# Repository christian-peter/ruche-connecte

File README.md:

# !!! EN COURS DE REDACTION !!! 
donc incomplet et en évolution à un rythme aléatoire

# Outil de suivi de ruchers
Ce projet est en cours de développement. Tous les éléments décrits dans le synoptique ne sont donc pas fonctionnels à ce jour.

Certains éléments ont été développés par des apprentis ingénieurs suivant la formation "électronique et informatique industrielle" à 
[Polytech Nice Sophia](http://unice.fr/polytechnice/fr). Une page spécifique à ce projet est disponible [ici](http://rucher.polytech.unice.fr/).  

L'objectif consiste à relever différents paramètres (masse, vibrations, température et hygrométrie interne à la ruche, données météorologiques) pour les rendre accessibles à distance via des périphériques tels qu'un ordinateur, une tablette, un smartphone ....  
 
Afin de remplir ces différentes fonctions, le système global à été scindé en plusieurs blocs. Les fonctions des trois premiers modules, qui doivent être autonomes en énergie, sont les suivantes :

* relever la masse de la ruche ;
* mesurer les grandeurs internes (températures, hygrométrie, vibrations, ....) ;
* mesurer les données météorologiques (température, hygrométrie, vent, pluie, ensoleillement, ...).

Les données relevées par ces modules sont transmises via un réseau LoRa, dont la portée doit être importante, à une passerelle dont la fonction consiste à enregistrer ces mesures dans une base de données. Ces données sont alors rendues accessibles via un serveur "web". 

L'électronique a été développée autour d'un microcontrôleur [ESP32](http://esp32.net/) d'Espressif Systems, basé sur l'architecture Xtensa LX6 de Tensilica, intégrant la gestion du Wi-Fi et du Bluetooth et d'un modem LoRa [RFM95](https://www.hoperf.com/modules/lora/RFM95.html).

Elle a été conçue avec un soucis de polyvalence pour permettre différentes configurations mais aussi pour faciliter les évolutions ou optimisations futures. C'est la cas notamment pour l'alimentation des différents modules.

## L'alimentation des modules

La tension d'alimentation des circuits précités est de 3.3V (maxi 3.6V). Il peuvent donc être alimentés directement par des batteries lithium-fer-phosphate (LiFePO<sub>4</sub>). Afin de pouvoir utiliser également d'autres sources d'énergie (batteries Lipo, Liion, plomb, .... ) les cartes sont équipées d'un régulateur de tension (MIC5239).

Une carte batterie spécifique peut être connectée via les connecteurs JP2 et JP3, elle peut être équipée d'une batterie LiFePO<sub>4</sub> connectée entre la masse et le signal '3.3_BAT'.

En l'absence d'alimentation sur l'entrée '+12V', le transistor Q4 est passant alimentant ainsi les éléments connectés à 'Vcc' à partir de la batterie LiFePO<sub>4</sub>. 

Si la carte est alimentée par l'entrée '+12V', les éléments connectés à 'Vcc' sont alimentés par le régulateur MIC5239. Le transistor Q4 est bloqué car le régulateur ne doit pas charger la batterie. L'entrée '+12V' peut recevoir des tensions comprises entre 3.6V et 30V. 
<!-- Les cartes sont généralement prévues pour recevoir un régulateur en boîtier :

* soit SOT-223,
* soit MSOP.-->

Dans le but d'économiser l'énergie, les périphériques ne sont alimentés par 'V+' que lorsque le transistor Q1 est passant (cad lorsque la sortie 'MEASURE' de l'ESP32 est au niveau haut).

## La programmation du microcontrôleur

Le logiciel est développé sur l'interface arduino. L’installation et l'utilisation de cet outil est décrit
[ici](https://www.arduino-france.com/tutoriels/ide-arduino-installation-et-utilisation/).

Il faut le configurer pour pouvoir utiliser l'ESP32 : voir 
[ce site](http://electroniqueamateur.blogspot.com/2019/07/programmer-lesp32-avec-lide-arduino.html)
ou [celui-ci](http://emery.claude.free.fr/esp32-idearduino.html).

Sauf erreur et/ou oubli, les librairies utilisées sont : 

* [DebugUtils](https://github.com/SensorsIot/DebugUtils/blob/master/DebugUtils/DebugUtils.h)
* [LoRa (Sandeep Mistry)](https://github.com/sandeepmistry/arduino-LoRa)
* [esp8266-oled-ssd1306](https://github.com/ThingPulse/esp8266-oled-ssd1306)
* [SparkFun NAU7802](https://github.com/sparkfun/SparkFun_Qwiic_Scale_NAU7802_Arduino_Library)
* [OneWire](https://www.pjrc.com/teensy/td_libs_OneWire.html)
* [CRC32](https://github.com/bakercp/CRC32)
* [MAX17263-fuel-gauge](https://github.com/avandalen/Arduino-MAX17263-fuel-gauge-library)
* [Streaming](https://github.com/janelia-arduino/Streaming)

Le téléversement nécessite un interface 
[USB/FTDI232](https://www.google.com/search?q=ftdi232&tbm=isch&ved=2ahUKEwj_ld-KopTvAhUEgM4BHXQxAnQQ2-cCegQIABAA&oq=ftdi232&gs_lcp=CgNpbWcQAzIECCMQJzIECCMQJzICCAAyAggAMgQIABAeMgQIABAeMgQIABAeMgQIABAeMgQIABAeMgYIABAKEBhQ8tsCWPLbAmDG3QJoAHAAeACAAViIAViSAQExmAEAoAEBqgELZ3dzLXdpei1pbWfAAQE&sclient=img&ei=FZQ_YL-3KYSAur4P9OKIoAc&bih=596&biw=1417&client=ubuntu&hs=15p).

Les connexions minimales à établir sont :

* ESP32 gnd <=> FTDI232 gnd (noir)
* ESP32 Tx <=> FTDI232 Rx (orange)
* ESP32 Rx <=> FTDI232 Tx (jaune)

Si le module n'est pas alimenté de façon autonome, il faut ajouter un fil d'alimentation (Vcc) et le cavalier jaune (voir la flèche) doit être positionné coté 3.3V, si le module dispose de sa propre alimentation il faut retirer le cavalier.

* ESP32 Vcc <=> FTDI232 Vcc (rouge)

Pour activer le mode téléversement il faut : appuyer sur le bouton 'PROG', appuyer et relâcher le bouton 'RST', 
relâcher le bouton 'PROG'.

Pour automatiser le transfert, j'ai développé un 
[petit module](/usb-ftdi232/README.md)
sur lequel on peut souder le module FTDI 232. 
Les connexions sont alors à réaliser sur le circuit secondaire et il faut ajouter :

* ESP32 IO0 <=> FTDI232 IO0 (vert)
* ESP32 RST <=> FTDI232 RST (marron)

Le connecteur JST permet d'alimenter l'ESP32, il faut alors retirer le cavalier d'alimentation.

# La réalisation 

* [la balance](/Balance/README.md#la-balance)
* le module interne
* le module météorologique
* la carte batterie
* la passerelle (gateway)

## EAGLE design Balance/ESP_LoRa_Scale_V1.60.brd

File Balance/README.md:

# LA BALANCE

## Préambule

Pour la partie mécanique qui ne sera pas développée ici (mis à part quelques photos de prototypes), je me suis inspiré des balances trouvées dans le commerce dont les capteurs de force sont de ce type :

Mon premier prototype avec un capteur n'était pas assez stable à mon gout. J'en ai donc réalisé 
[d'autres](/Balance/Images/proto_meca.png) avec 2 capteurs puis 4 capteurs. 

J'ai aussi testé les capteurs utilisés pour les pèse-personnes.

L'électronique est donc conçue pour s'adapter à ces différentes configurations. 

## Fonctionnement

Après mise sous tension, le module entre en mode sommeil pour réduire la consommation au maximum.
Il se réveille à intervalles réguliers. Il mesure alors la masse et envoie les données (avec un code d'erreur CRC) via un réseau LoRa puis attend un accusé de réception. A réception d'un accusé de réception valide, le module repasse en mode sommeil ; si l'accusé de réception n'est pas valide, les données sont renvoyées (au maximum 'send_max_tries' fois). Sans accusé de réception au bout de 'WAIT_TIME_FOR_ACKNOWLEDGE' le module passe en mode sommeil.

La durée de sommeil est paramétrable et différenciée entre jour et nuit. La période 'jour' débute 1 heure avant le début du jour et s'achève 1 heure après la fin du jour.

Le module peut aussi être réveillé manuellement par un appui bref sur la touche capacitive gauche ; un menu à dérouler avec la touche capacitive droite permet alors de sélectionner différentes actions ou d'afficher différentes informations :

* création d'une visite (dans la base de données),
* mise en sommeil,
* nourrissement 50/50 (1),
* nourrissement 70/30 (1),
* nourrissement candy (1),
* modification matérielle (1),
* mesure de la masse,
* informations batterie,
* informations version et numéro de balance,
* informations LoRa,
* informations température capteurs.

Une fois le choix validé par la touche capacitive gauche, les données sont envoyées ou les informations affichées et le module retourne au mode sommeil.

(1) L'information ainsi que la variation de masse correspondante est stockée dans la base de données.

## Calibration et réglages

Un appui maintenu sur la touche capacitive gauche permet d'accéder à la procédure de calibration ou au réglage des paramètres.

### Calibration

Avant la première utilisation, il faut calibrer la balanceen suivant les indications affichées sur l'écran LCD.

### Réglages

Un certain nombre de paramètres sont modifiables en se connectant au module en Bluetooth avec un terminal série : par exemple 
[Serial Bluetooth Terminal](https://play.google.com/store/apps/details?id=de.kai_morich.serial_bluetooth_terminal&hl=fr&gl=US).

Les paramètres sont regroupés par famille et sont les suivants :

* réglages généraux :
    - intervalle de mesure le jour,
    - intervalle de mesure la nuit,
    - intervalle de mesure pour visite,
    - nombre maximum de transmission,
    - numéro de la balance,
    - variation de masse générant une alerte,
* réglages LoRa :
    - fréquence, 
    - facteur d’étalement de spectre (7 à 12; 12 <=> portée maximale, mais autonomie plus faible),
    - bande passante,
    - puissance d'émission (7 à 15 dB <=> portée maximale, mais autonomie plus faible),
* dérive des capteurs en température,
* initialisation de la mémoire EEPROM (reset des paramètres de calibration et autres réglages).

exemple vidéo : [mp4](http://rucher.polytech.unice.fr/ruche-connecte/videos/reglages.mp4) 
[wmv](http://rucher.polytech.unice.fr/ruche-connecte/videos/reglages.wmv)
<!-- 
ffmpeg -i /tmp/reglages.mp4 -vf scale=960:-1  -an output2.mp4
https://www.linuxtricks.fr/wiki/ffmpeg-la-boite-a-outils-multimedia
https://tuxicoman.jesuislibre.net/2017/01/changer-la-resolution-dune-video-avec-ffmpeg-sous-linux.html
-->

## Electronique

Les schémas et PCB sont dessinés avec [eagle](https://www.autodesk.com/products/eagle/overview?plc=F360&term=1-YEAR&support=ADVANCED&quantity=1) :

* [schéma](/Balance/ESP_LoRa_Scale_V1.60.sch)
* [pcb](/Balance/ESP_LoRa_Scale_V1.60.brd)
* [gerber](/Balance/gerber/ESP_LoRa_Scale_V1.60.zip)
* [liste du matériel](/Balance/ESP_LoRa_Scale_V1.60.csv)

L'[antenne 'UCA'](http://users.polytech.unice.fr/~ferrero/recherche_UCAboards.html) 
LoRa, déssinée par Fabien Ferrero, est supportée par le circuit imprimé. 
Pour une efficacité maximale de l'antenne, ce dernier doit être réalisé en FR4 avec une épaisseur de 0,8mm.

Il est aussi possible de connecter une antenne externe via un connecteur UFL, la piste reliée à l'antenne 'UCA'
doit alors être coupée.  

Cette carte peut recevoir 1, 2 ou 4 capteurs de force. Le convertisseur NAU7802 U4 et les composants associés
ne sont utiles que pour l'utilisation de 4 capteurs ; le pont SJ7 doit alors être court-circuité.
Avec 1 ou 2 capteurs on laisse SJ7 ouvert pour réduire la consommation et on utilise les entrées du convertisseur U2.
Un capteur unique doit être connecté sur les entrées 'A', les entrées 'B' étant reliées à la masse.

Le connecteur 'JP3' permet de connecter un capteur de température dans le but de compenser les dérives thermiques des capteurs de force. Pour l'instant seul est supporté le capteur de type 18B20. On pourrait aussi utiliser des capteurs de la famille DHT11,
permettant d'obtenir aussi une mesure d'hygrométrie mais la partie software devra être modifiée en conséquence.

## Logiciel

L'archive est à extraire dans le dossier 'projet' de l'IDE arduino.

* [ESP_LoRa_Scale_V0.34.zip](/Balance/ESP_LoRa_ScaleV0.34.zip)

Hormis la mesure de tension de la batterie, la partie 'fuel gauge' reste à développer.

## Mesures

à venir

## Prototypes

aussi

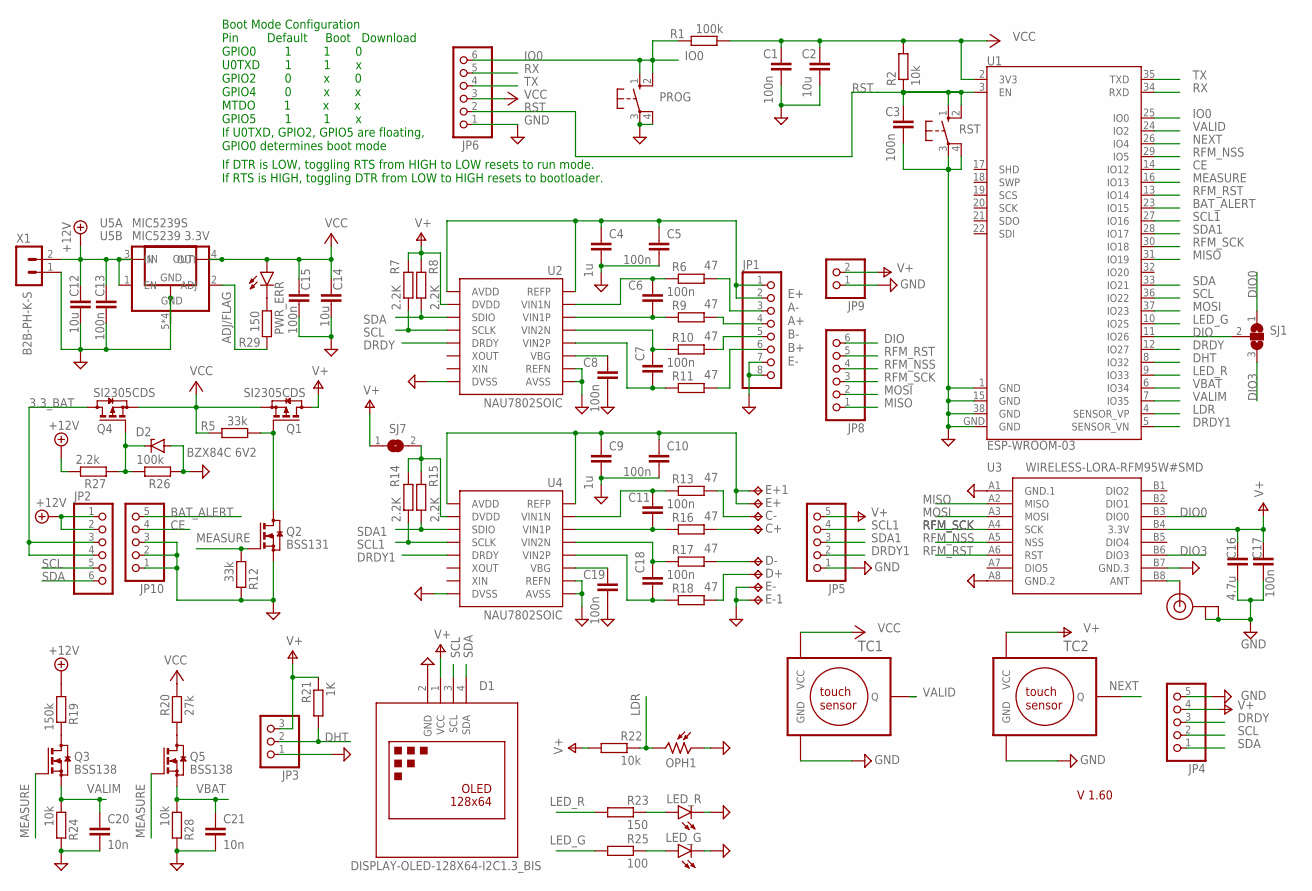
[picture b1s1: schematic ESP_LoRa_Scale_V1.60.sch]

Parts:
C1, C3, C5, C6, C7, C8, C10, C11, C13, C15, C17, C18, C19: 100n; C1206
C2, C12, C14: 10u; C1210
C4, C9: 1u; C1210
C16: 4.7u; C1210
C20, C21: 10n; C1206
C+: TPTP17SQ; TP17SQ
C-: TPTP17SQ; TP17SQ
D1: DISPLAY-OLED-128X64-I2C1.3_BIS; DISPLAY-OLED-128X64-1.3-I2C_BIS
D2: BZX84C 6V2; TO236
D+: TPTP17SQ; TP17SQ
D-: TPTP17SQ; TP17SQ
E+, E+1: TPTP17SQ; TP17SQ
E-, E-1: TPTP17SQ; TP17SQ
J1: U.FL
JP1: PINHD-1X8; 1X08
JP2, JP6, JP8: PINHD-1X6; 1X06
JP3: PINHD-1X3; 1X03
JP4, JP5, JP10: PINHD-1X5; 1X05
JP9: PINHD-1X2; 1X02
LED_G: LEDSMT1206; 1206
LED_R: LEDSMT1206; 1206
OPH1: VT93N2; VT900
PROG: 10-XX; B3F-10XX
PWR_ERR: LEDSMT1206; 1206
Q1, Q4: SI2305CDS; SOT23
Q2: BSS131; SOT23
Q3, Q5: BSS138; SOT23
R1, R26: 100k; R1206
R2, R22, R24, R28: 10k; R1206
R5, R12: 33k; R1206
R6, R9, R10, R11, R13, R16, R17, R18: 47; R1206
R7, R8, R14, R15: 2.2K; R1206
R19: 150k; R1206
R20: 27k; R1206
R21: 1K; R1206
R23, R29: 150; R1206
R25: 100; R1206
R27: 2.2k; R1206
RST: 10-XX; B3F-10XX
SJ1: SJ2W; SJ_2
SJ7: SJ
TC1, TC2: TTP223R_H; TTP233RED_H
U1: ESP-WROOM-03
U2, U4: NAU7802SOIC; SO16
U3: WIRELESS-LORA-RFM95W#SMD
U5A: MIC5239 3.3V; MSOP08
U5B: MIC5239S; SOT223
X1: B2B-PH-K-S

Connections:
3.3_BAT: JP2.3, JP2.4, Q4.3 (D)
+12V: C12.1, C13.1, JP2.1, JP2.2, R19.1, R27.2, U5A.1 (EN), U5A.3 (IN), U5B.1 (IN), X1.2
A+: JP1.4, R9.2
A-: JP1.3, R6.2
ADJ/FLAG: R29.2, U5A.2 (ADJ)
ANT: J1.3 (SIGNAL), U3.B8 (ANT)
B+: JP1.6, R11.2
B-: JP1.5, R10.2
BAT_ALERT: JP10.5, U1.23 (IO15)
CE: JP10.4, U1.14 (IO12)
DHT: JP3.2, R21.1, U1.8 (IO32)
DIO: JP8.6, SJ1.2, U1.11 (IO26)
DIO0: SJ1.1, U3.B3 (DIO0)
DIO3: SJ1.3, U3.B6 (DIO3)
DRDY: JP4.3, U1.12 (IO27), U2.12 (DRDY)
DRDY1: JP5.2, U1.5 (SENSOR_VN), U4.12 (DRDY)
GND: C1.2, C2.2, C3.2, C4.2, C5.2, C8.2, C9.2, C10.2, C12.2, C13.2, C14.2, C15.2, C16.2, C17.2, C19.2, C20.2, C21.2, D1.2 (GND), D2.A, E-.TP, E-1.TP, J1.1 (GND), J1.2 (GND), JP1.7, JP1.8, JP3.1, JP4.5, JP5.1, JP6.1, JP9.1, JP10.1, JP10.2, JP10.3, LED_G.C, LED_R.C, OPH1.1, PROG.3, PROG.4 (P1), Q2.2 (S), R12.2, R24.2, R26.1, R28.2, RST.3, RST.4 (P1), TC1.P$3 (GND), TC2.P$3 (GND), U1.1 (GND), U1.15 (GND), U1.38 (GND), U1.GND, U2.7 (REFN), U2.8 (AVSS), U2.9 (DVSS), U3.A1 (GND.1), U3.A8 (GND.2), U3.B7 (GND.3), U4.7 (REFN), U4.8 (AVSS), U4.9 (DVSS), U5A.5 (GND), U5A.6 (GND), U5A.7 (GND), U5A.8 (GND), U5B.2 (GND), U5B.4 (GND), X1.1
IO0: JP6.6, PROG.1 (S), PROG.2 (S1), R1.2, U1.25 (IO0)
LDR: OPH1.2, R22.2, U1.4 (SENSOR_VP)
LED_G: R25.1, U1.10 (IO25)
LED_R: R23.1, U1.9 (IO33)
MEASURE: Q2.1 (G), Q3.1 (G), Q5.1 (G), R12.1, U1.16 (IO13)
MISO: JP8.1, U1.31 (IO19), U3.A2 (MISO)
MOSI: JP8.2, U1.37 (IO23), U3.A3 (MOSI)
unnamed: Q1.1 (G), Q2.3 (D), R5.1
unnamed: Q3.3 (D), R19.2
unnamed: R14.2, R15.2, SJ7.2, U4.15 (DVDD)
unnamed: Q5.3 (D), R20.1
unnamed: PWR_ERR.C, R29.1
unnamed: LED_R.A, R23.2
unnamed: LED_G.A, R25.2
unnamed: C8.1, U2.6 (VBG)
unnamed: C19.1, U4.6 (VBG)
unnamed: C11.2, R16.1, U4.3 (VIN1P)
unnamed: C11.1, R13.1, U4.2 (VIN1N)
unnamed: C6.2, R9.1, U2.3 (VIN1P)
unnamed: C6.1, R6.1, U2.2 (VIN1N)
unnamed: C7.1, R10.1, U2.4 (VIN2N)
unnamed: C7.2, R11.1, U2.5 (VIN2P)
unnamed: C18.1, R17.1, U4.4 (VIN2N)
unnamed: C18.2, R18.1, U4.5 (VIN2P)
unnamed: D+.TP, R18.2
unnamed: D-.TP, R17.2
unnamed: C9.1, C10.1, E+.TP, E+1.TP, U4.1 (REFP), U4.16 (AVDD)
unnamed: C-.TP, R13.2
unnamed: C+.TP, R16.2
unnamed: C4.1, C5.1, JP1.1, JP1.2, U2.1 (REFP), U2.16 (AVDD)
unnamed: D2.C, Q4.1 (G), R26.2, R27.1
NEXT: TC2.P$2 (Q), U1.26 (IO4)
RFM_NSS: JP8.4, U1.29 (IO5), U3.A5 (NSS)
RFM_RST: JP8.5, U1.13 (IO14), U3.A6 (RST)
RFM_SCK: JP8.3, U1.30 (IO18), U3.A4 (SCK)
RST: C3.1, JP6.2, R2.1, RST.1 (S), RST.2 (S1), U1.3 (EN)
RX: JP6.5, U1.34 (RXD)
SCL: D1.3 (SCL), JP2.5, JP4.2, R7.1, U1.36 (IO22), U2.13 (SCLK)
SCL1: JP5.4, R14.1, U1.27 (IO16), U4.13 (SCLK)
SDA: D1.4 (SDA), JP2.6, JP4.1, R8.1, U1.33 (IO21), U2.14 (SDIO)
SDA1: JP5.3, R15.1, U1.28 (IO17), U4.14 (SDIO)
TX: JP6.4, U1.35 (TXD)
V+: C16.1, C17.1, D1.1 (VCC), JP3.3, JP4.4, JP5.5, JP9.2, Q1.3 (D), R7.2, R8.2, R21.2, R22.1, SJ7.1, TC2.P$1 (VCC), U2.15 (DVDD), U3.B4 (3.3V)
VALID: TC1.P$2 (Q), U1.24 (IO2)
VALIM: C20.1, Q3.2 (S), R24.1, U1.7 (IO35)
VBAT: C21.1, Q5.2 (S), R28.1, U1.6 (IO34)
VCC: C1.1, C2.1, C14.1, C15.1, JP6.3, PWR_ERR.A, Q1.2 (S), Q4.2 (S), R1.1, R2.2, R5.2, R20.2, TC1.P$1 (VCC), U1.2 (3V3), U5A.4 (OUT), U5B.3 (OUT)

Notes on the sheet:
If DTR is LOW, toggling RTS from HIGH to LOW resets to run mode. If RTS is HIGH, toggling DTR from LOW to HIGH resets to bootloader.
Boot Mode Configuration Pin Default Boot Download GPIO0 1 1 0 U0TXD 1 1 x GPIO2 0 x 0 GPIO4 0 x x MTDO 1 x x GPIO5 1 1 x If U0TXD, GPIO2, GPIO5 are floating, GPIO0 determines boot mode
V 1.60
E+ A- A+ B- B+ E-

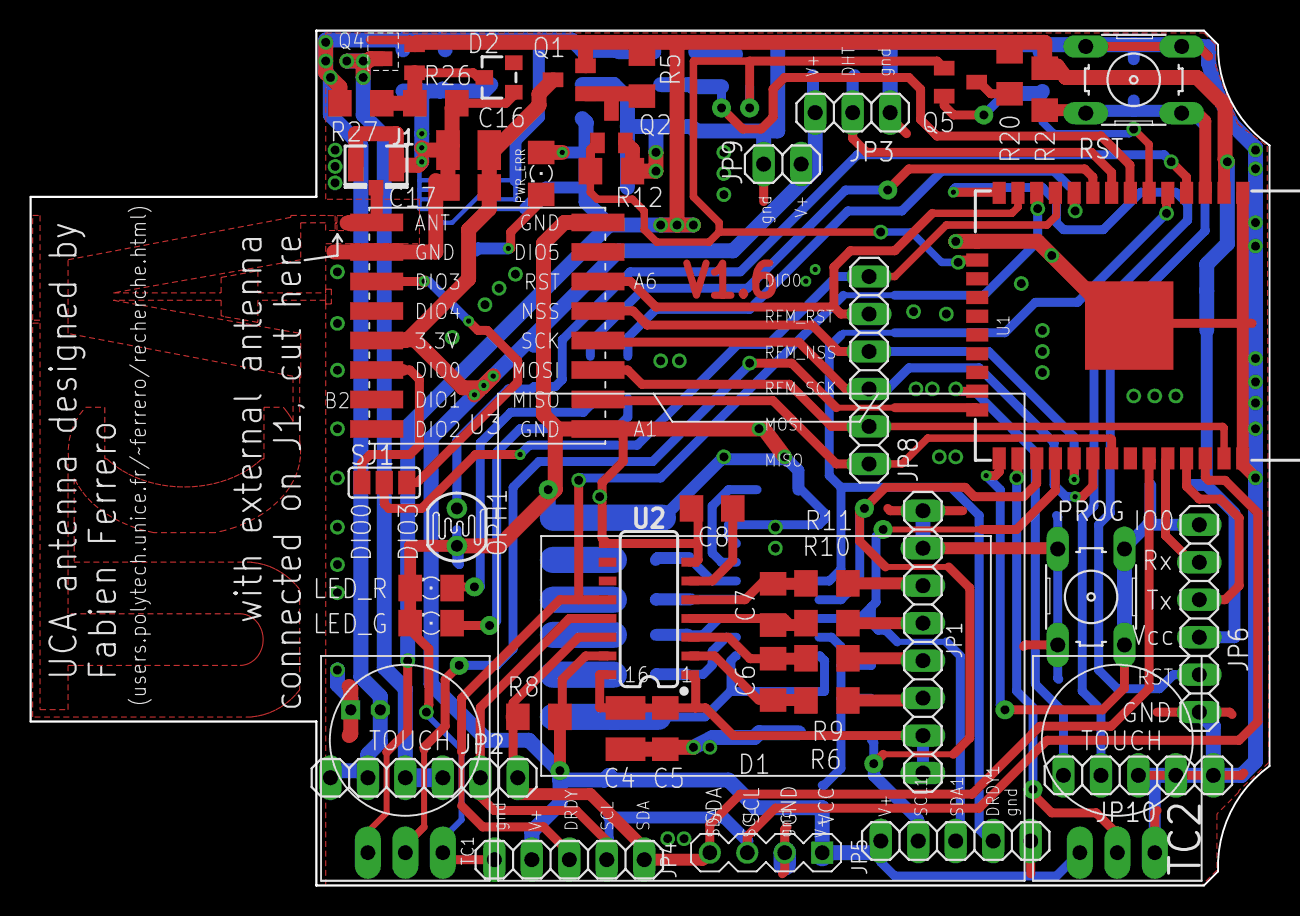
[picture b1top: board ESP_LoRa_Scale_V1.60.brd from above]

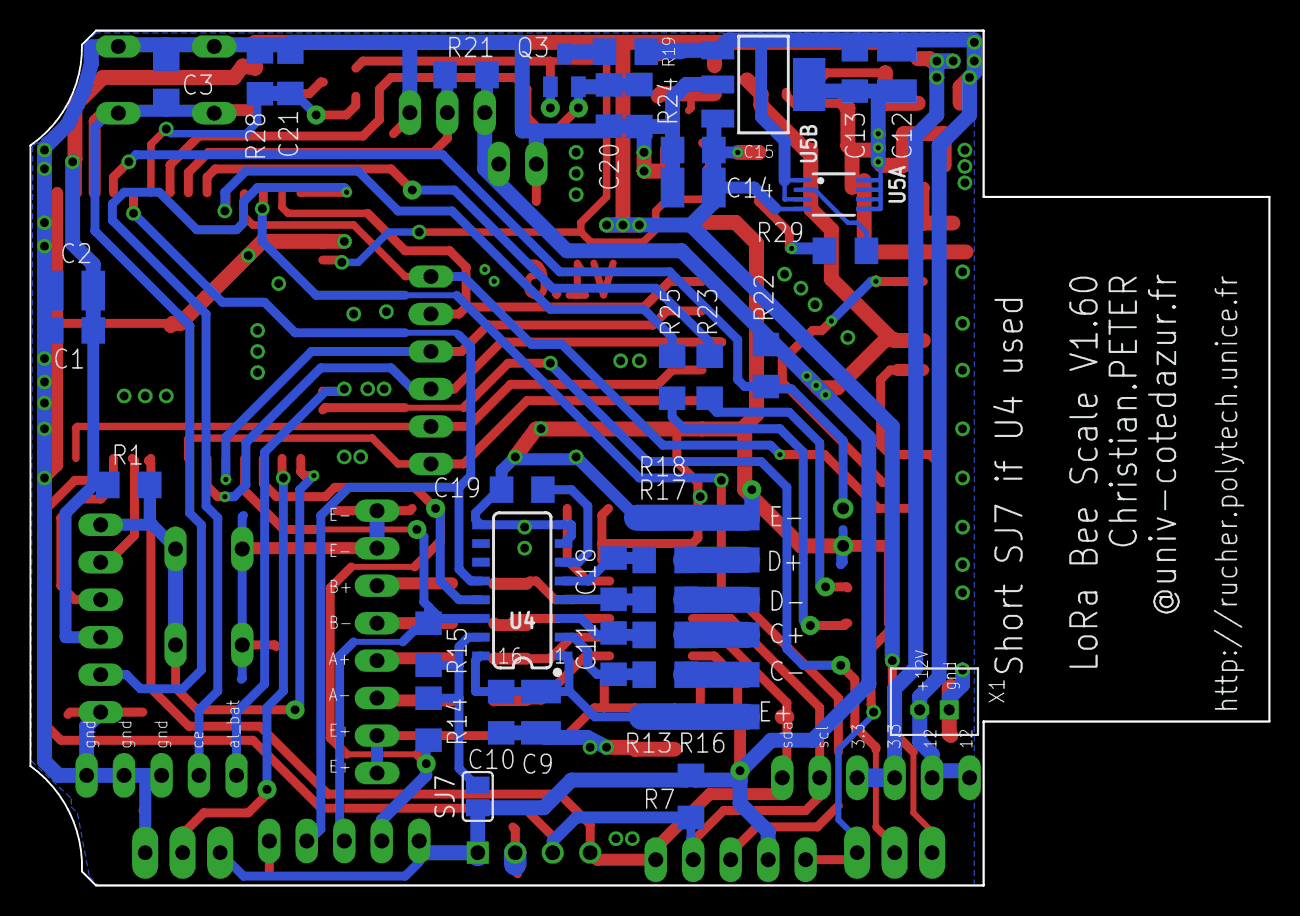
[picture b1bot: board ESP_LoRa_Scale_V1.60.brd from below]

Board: 2 copper layers, 84.0 x 57.9 mm, 90 parts (44 on the bottom side), 64 nets.

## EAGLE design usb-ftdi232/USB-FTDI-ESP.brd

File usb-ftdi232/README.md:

Les schémas et PCB sont dessinés avec [eagle](https://www.autodesk.com/products/eagle/overview?plc=F360&term=1-YEAR&support=ADVANCED&quantity=1) :

* [schéma](/usb-ftdi232/USB-FTDI-ESP.sch)
* [pcb](/usb-ftdi232/USB-FTDI-ESP.brd)
* [gerber](/usb-ftdi232/gerber/USB-FTDI-ESP32.zip)
* [liste du matériel](/usb-ftdi232/USB-FTDI-ESP.csv)

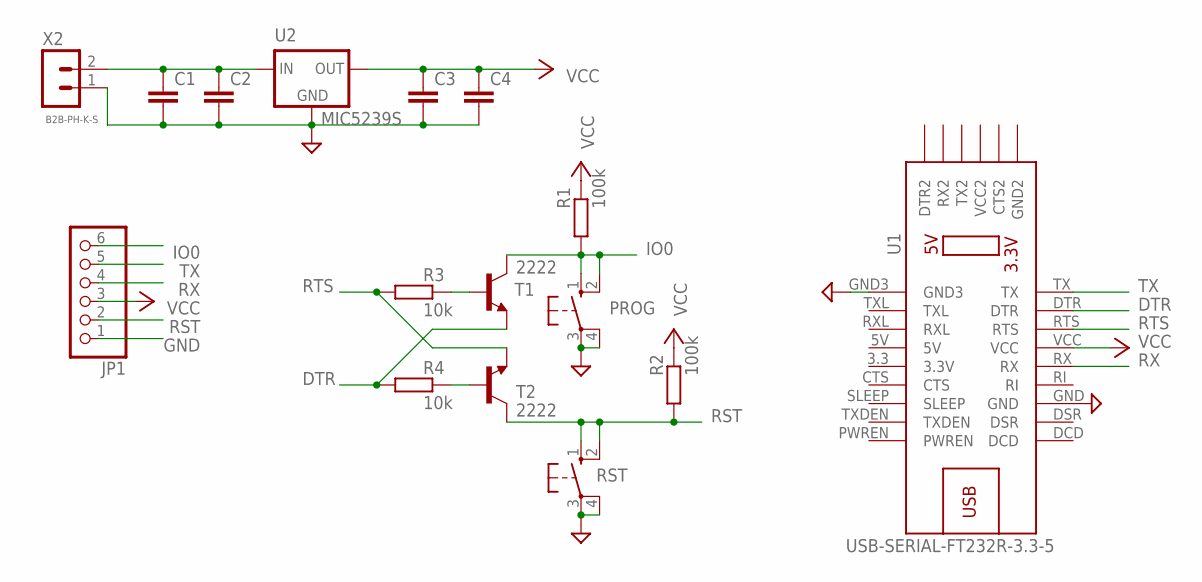
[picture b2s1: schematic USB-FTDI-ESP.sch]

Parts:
C1, C2, C3, C4: C-EUC1206K; C1206K
JP1: PINHD-1X6; 1X06
PROG: 10-XX; B3F-10XX
R1, R2: 100k; R1206
R3, R4: 10k; R1206
RST: 10-XX; B3F-10XX
T1, T2: 2222; SOT23-BEC
U1: USB-SERIAL-FT232R-3.3-5
U2: MIC5239S; SOT223
X2: B2B-PH-K-S

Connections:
DTR: R4.1, T1.E, U1.DTR
GND: C1.2, C2.2, C3.2, C4.2, JP1.1, PROG.3, PROG.4 (P1), RST.3, RST.4 (P1), U1.GND, U1.GND3, U2.2 (GND), U2.4 (GND), X2.1
IO0: JP1.6, PROG.1 (S), PROG.2 (S1), R1.1, T1.C
unnamed: C1.1, C2.1, U2.1 (IN), X2.2
unnamed: R3.2, T1.B
unnamed: R4.2, T2.B
RST: JP1.2, R2.1, RST.1 (S), RST.2 (S1), T2.C
RTS: R3.1, T2.E, U1.RTS
RX: JP1.4, U1.RX
TX: JP1.5, U1.TX
VCC: C3.1, C4.1, JP1.3, R1.2, R2.2, U1.VCC, U2.3 (OUT)
VCC2: U1.VCC2

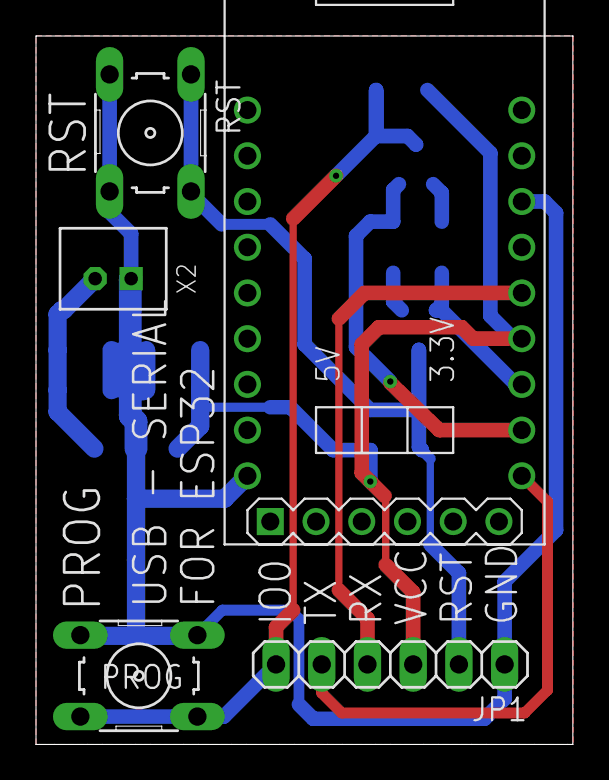
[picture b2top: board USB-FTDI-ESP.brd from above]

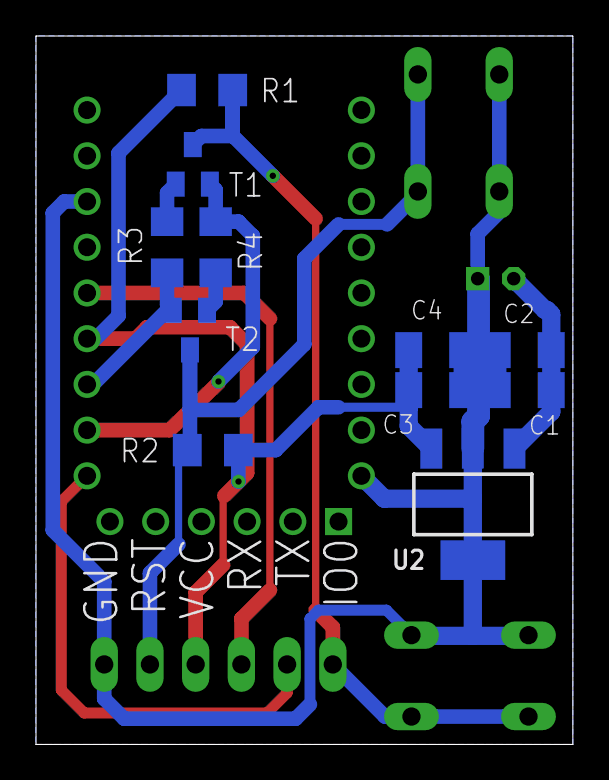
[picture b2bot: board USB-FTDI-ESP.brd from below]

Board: 2 copper layers, 29.8 x 39.4 mm, 16 parts (11 on the bottom side), 11 nets.

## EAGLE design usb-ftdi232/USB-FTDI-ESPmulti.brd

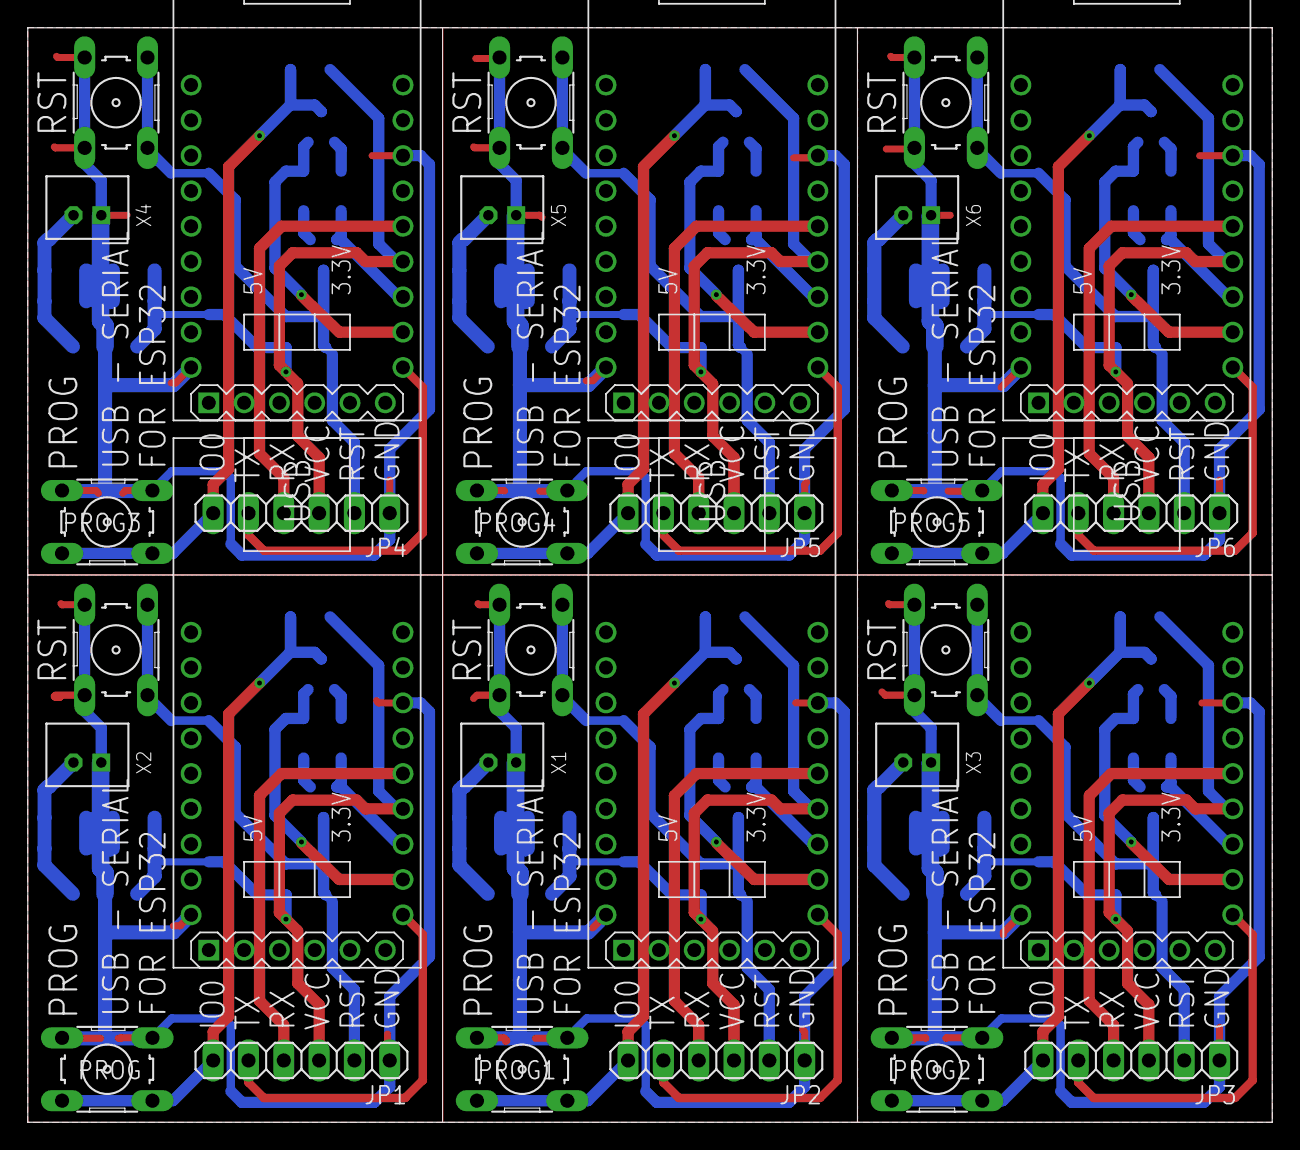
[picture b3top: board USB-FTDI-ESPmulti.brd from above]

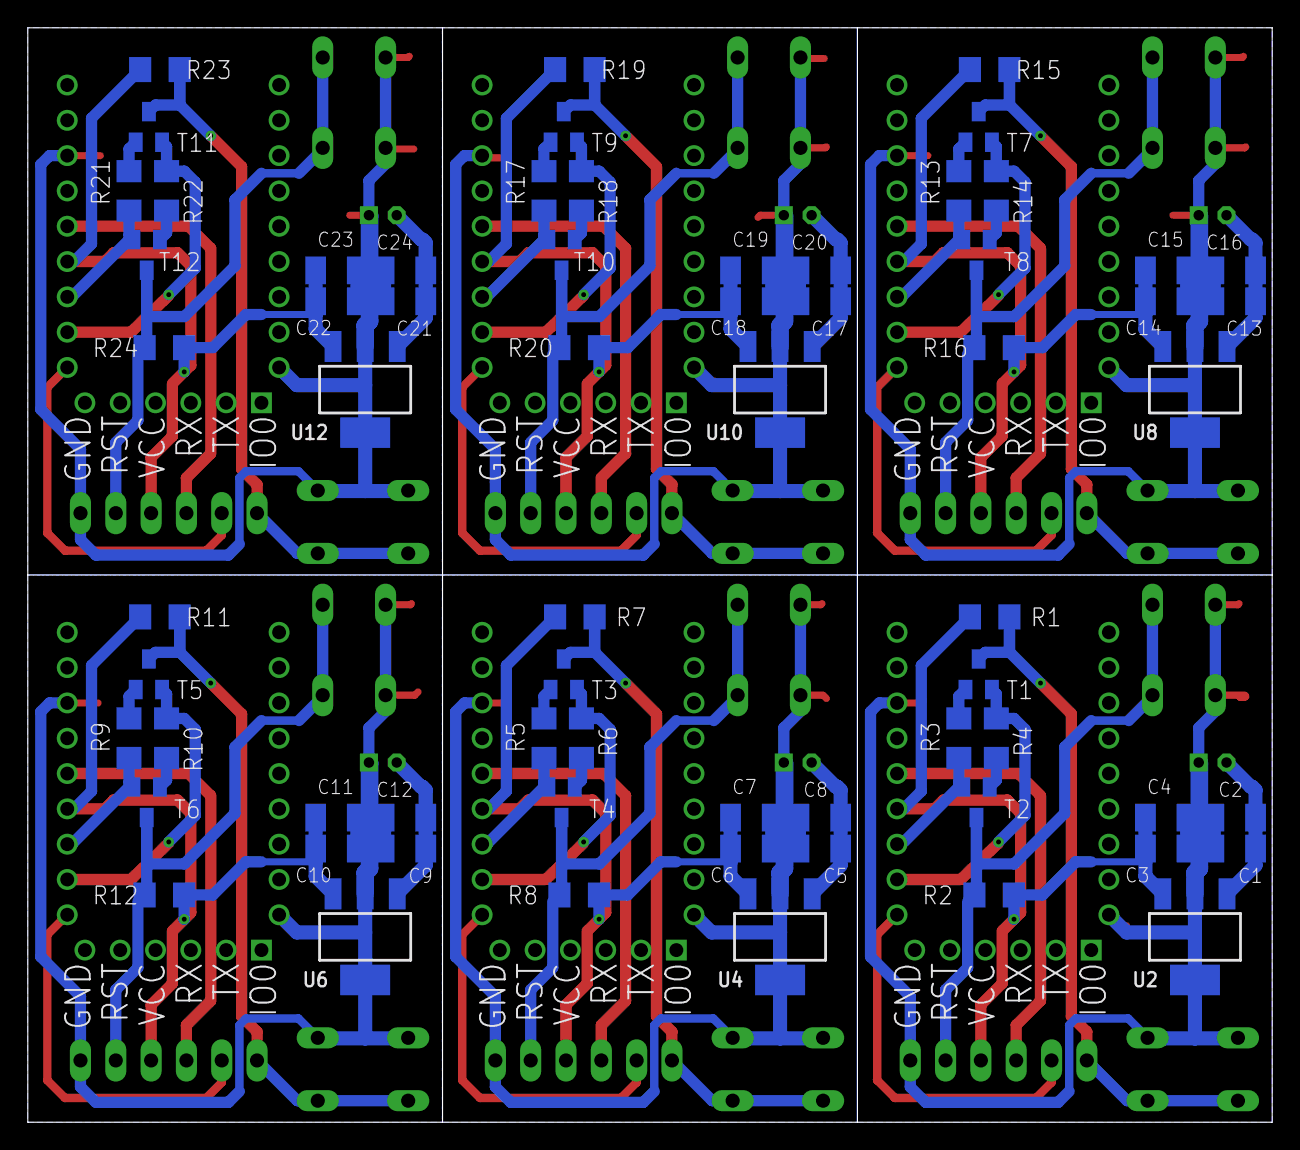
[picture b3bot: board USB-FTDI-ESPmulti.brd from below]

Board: 2 copper layers, 89.5 x 78.7 mm, 96 parts (66 on the bottom side), 66 nets.

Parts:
C1, C2, C3, C4, C5, C6, C7, C8, C9, C10, C11, C12, C13, C14, C15, C16, C17, C18, C19, C20, C21, C22, C23, C24: C1206K
JP1, JP2, JP3, JP4, JP5, JP6: 1X06
PROG, PROG1, PROG2, PROG3, PROG4, PROG5: B3F-10XX
R1, R2, R7, R8, R11, R12, R15, R16, R19, R20, R23, R24: 100k; R1206
R3, R4, R5, R6, R9, R10, R13, R14, R17, R18, R21, R22: 10k; R1206
RST, RST1, RST2, RST3, RST4, RST5: B3F-10XX
T1, T2, T3, T4, T5, T6, T7, T8, T9, T10, T11, T12: 2222; SOT23-BEC
U1, U3, U5, U7, U9, U11: USB-SERIAL-FT232R-3.3-5
U2, U4, U6, U8, U10, U12: MIC5239S; SOT223
X1, X2, X3, X4, X5, X6: B2B-PH-K-S

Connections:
DTR: R4.1, T1.E, U1.DTR
DTR1: R6.1, T3.E, U3.DTR
DTR2: R10.1, T5.E, U5.DTR
DTR3: R14.1, T7.E, U7.DTR
DTR4: R18.1, T9.E, U9.DTR
DTR5: R22.1, T11.E, U11.DTR
GND: C1.2, C2.2, C3.2, C4.2, JP1.1, PROG.3, PROG.4, RST.3, RST.4, U1.GND, U1.GND3, U2.2, U2.4, X2.1
GND1: C5.2, C6.2, C7.2, C8.2, JP2.1, PROG1.3, PROG1.4, RST1.3, RST1.4, U3.GND, U3.GND3, U4.2, U4.4, X1.1
GND2: C9.2, C10.2, C11.2, C12.2, JP3.1, PROG2.3, PROG2.4, RST2.3, RST2.4, U5.GND, U5.GND3, U6.2, U6.4, X3.1
GND3: C13.2, C14.2, C15.2, C16.2, JP4.1, PROG3.3, PROG3.4, RST3.3, RST3.4, U7.GND, U7.GND3, U8.2, U8.4, X4.1
GND4: C17.2, C18.2, C19.2, C20.2, JP5.1, PROG4.3, PROG4.4, RST4.3, RST4.4, U9.GND, U9.GND3, U10.2, U10.4, X5.1
GND5: C21.2, C22.2, C23.2, C24.2, JP6.1, PROG5.3, PROG5.4, RST5.3, RST5.4, U11.GND, U11.GND3, U12.2, U12.4, X6.1
IO0: JP1.6, PROG.1, PROG.2, R1.1, T1.C
IO1: JP2.6, PROG1.1, PROG1.2, R7.1, T3.C
IO2: JP3.6, PROG2.1, PROG2.2, R11.1, T5.C
IO3: JP4.6, PROG3.1, PROG3.2, R15.1, T7.C
IO4: JP5.6, PROG4.1, PROG4.2, R19.1, T9.C
IO5: JP6.6, PROG5.1, PROG5.2, R23.1, T11.C
unnamed: C1.1, C2.1, U2.1, X2.2
unnamed: R5.2, T3.B
unnamed: R6.2, T4.B
unnamed: C5.1, C8.1, U4.1, X1.2
unnamed: R9.2, T5.B
unnamed: R10.2, T6.B
unnamed: C9.1, C12.1, U6.1, X3.2
unnamed: R13.2, T7.B
unnamed: R14.2, T8.B
unnamed: R3.2, T1.B
unnamed: C13.1, C16.1, U8.1, X4.2
unnamed: R17.2, T9.B
unnamed: R18.2, T10.B
unnamed: R4.2, T2.B
unnamed: C17.1, C20.1, U10.1, X5.2
unnamed: R21.2, T11.B
unnamed: R22.2, T12.B
unnamed: C21.1, C24.1, U12.1, X6.2
RST: JP1.2, R2.1, RST.1, RST.2, T2.C
RST1: JP2.2, R8.1, RST1.1, RST1.2, T4.C
RST2: JP3.2, R12.1, RST2.1, RST2.2, T6.C
RST3: JP4.2, R16.1, RST3.1, RST3.2, T8.C
RST4: JP5.2, R20.1, RST4.1, RST4.2, T10.C
RST5: JP6.2, R24.1, RST5.1, RST5.2, T12.C
RTS: R3.1, T2.E, U1.RTS
RTS1: R5.1, T4.E, U3.RTS
RTS2: R9.1, T6.E, U5.RTS
RTS3: R13.1, T8.E, U7.RTS
RTS4: R17.1, T10.E, U9.RTS
RTS5: R21.1, T12.E, U11.RTS
RX: JP1.4, U1.RX
RX1: JP2.4, U3.RX
RX2: JP3.4, U5.RX
RX3: JP4.4, U7.RX
RX4: JP5.4, U9.RX
RX5: JP6.4, U11.RX
TX: JP1.5, U1.TX
TX1: JP2.5, U3.TX
TX2: JP3.5, U5.TX
TX3: JP4.5, U7.TX
TX4: JP5.5, U9.TX
TX5: JP6.5, U11.TX
VCC: C3.1, C4.1, JP1.3, R1.2, R2.2, U1.VCC, U2.3
VCC1: C6.1, C7.1, JP2.3, R7.2, R8.2, U3.VCC, U4.3
VCC4: C10.1, C11.1, JP3.3, R11.2, R12.2, U5.VCC, U6.3
VCC6: C14.1, C15.1, JP4.3, R15.2, R16.2, U7.VCC, U8.3
VCC8: C18.1, C19.1, JP5.3, R19.2, R20.2, U9.VCC, U10.3
VCC10: C22.1, C23.1, JP6.3, R23.2, R24.2, U11.VCC, U12.3

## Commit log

2021-02-18 Create
    Les images

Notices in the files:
parts and their libraries:
diy-modules: Released under the Creative Commons Attribution 4.0 International License: http://creativecommons.org/licenses/by/4.0
SparkFun-IC-Conversion: Licensing: Creative Commons ShareAlike 4.0 International - https://creativecommons.org/licenses/by-sa/4.0
micrel: Copyright (C) 2008, Bob Starr
